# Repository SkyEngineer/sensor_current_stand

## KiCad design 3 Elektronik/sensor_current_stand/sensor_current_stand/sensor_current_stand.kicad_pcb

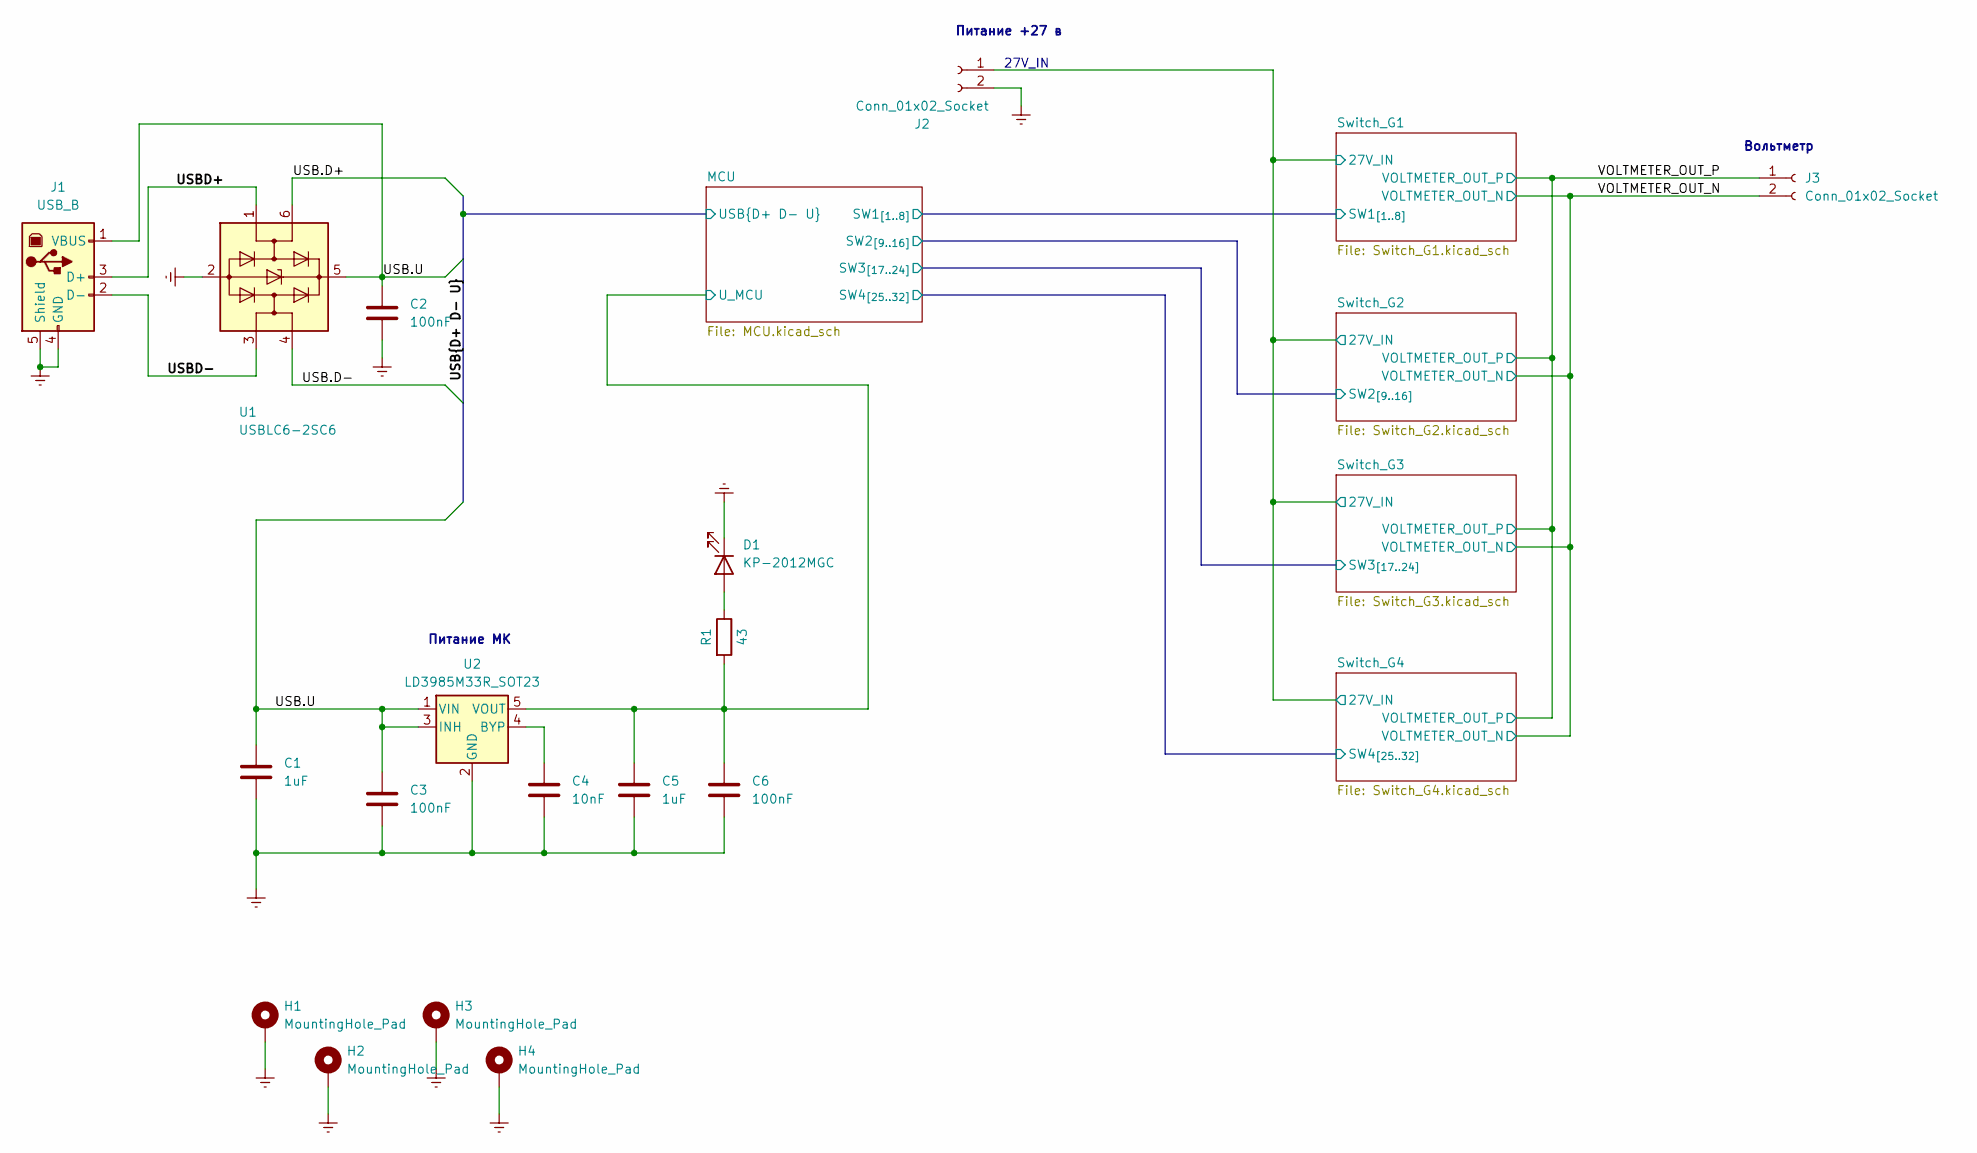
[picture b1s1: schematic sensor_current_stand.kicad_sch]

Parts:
C1, C5: 1uF; C_0805_2012Metric
C2, C3, C6: 100nF; C_0805_2012Metric
C4: 10nF; C_0805_2012Metric
D1: KP-2012MGC; LED_0805_2012Metric_Pad1.15x1.40mm_HandSolder
H1, H2, H3, H4: MountingHole_Pad; MountingHole_4.3mm_M4_Pad_TopBottom
J1: USB_B; USB_B_Lumberg_2411_02_Horizontal
J2, J3: Conn_01x02_Socket; JWT_A3963_1x02_P3.96mm_Vertical
R1: 43; R_1206_3216Metric_Pad1.30x1.75mm_HandSolder
U1: USBLC6-2SC6; SOT-23-6
U2: LD3985M33R_SOT23; SOT-23-5

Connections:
/MCU/U_MCU: C5.1, C6.1, R1.2, U2.5 (VOUT); also elsewhere on the board
/Switch_G1/27V_IN: J2.1; also elsewhere on the board
/USB.D+: U1.6 (I/O1); also elsewhere on the board
/USB.D-: U1.4 (I/O2); also elsewhere on the board
/USB.U: C1.1, C2.1, C3.1, J1.1 (VBUS), U1.5 (VBUS), U2.1 (VIN), U2.3 (INH)
/USBD+: J1.3 (D+), U1.1 (I/O1)
/USBD-: J1.2 (D-), U1.3 (I/O2)
/VOLTMETER_OUT_N: J3.2; also elsewhere on the board
/VOLTMETER_OUT_P: J3.1; also elsewhere on the board
unnamed: D1.2 (A), R1.1
unnamed: C4.1, U2.4 (BYP)

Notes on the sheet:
27V_IN
Вольтметр
Питание +27 в
Питание МК

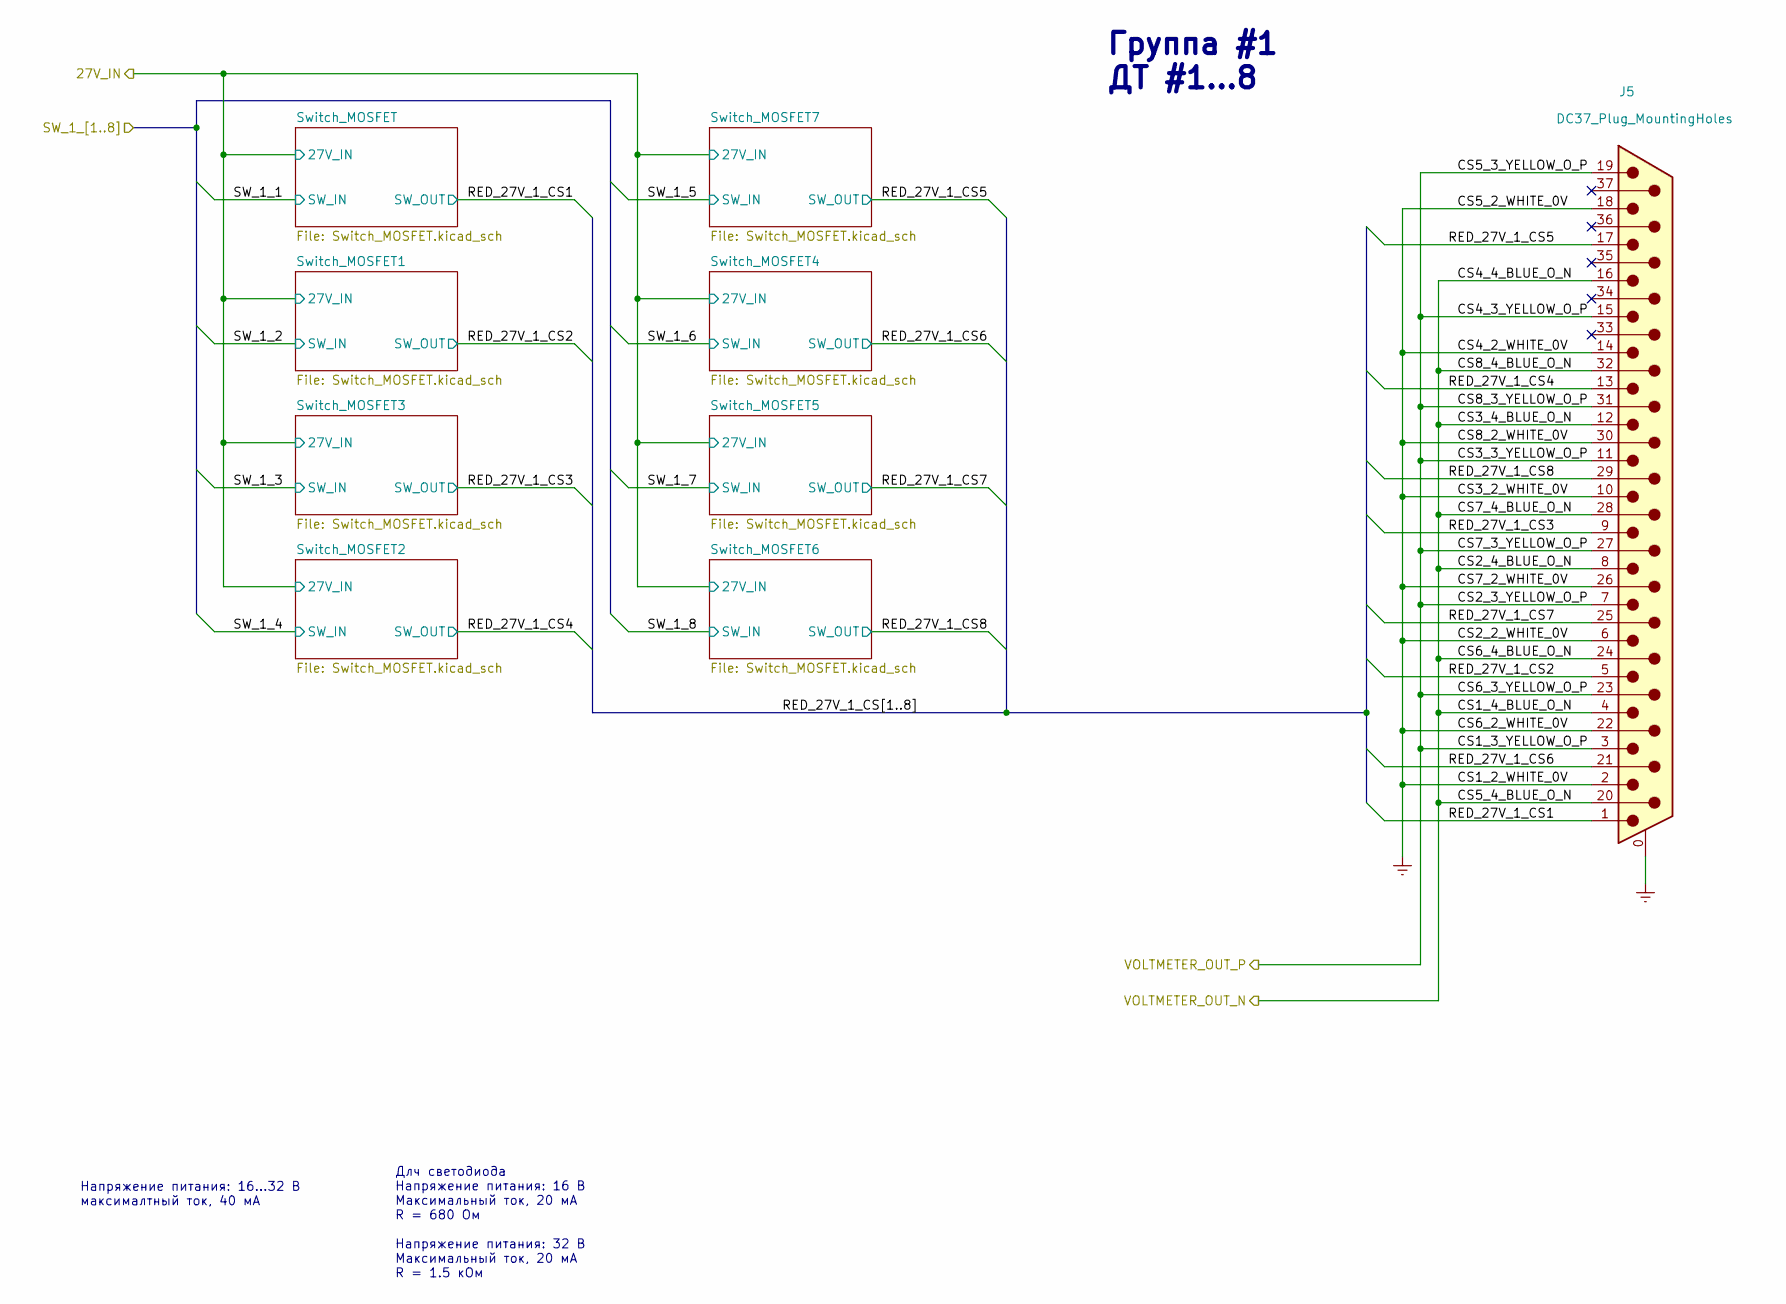
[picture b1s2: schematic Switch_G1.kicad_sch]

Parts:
J5: DC37_Plug_MountingHoles; DSUB-37_Male_Vertical_P2.77x2.84mm_MountingHoles

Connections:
/Switch_G1/27V_IN: J5.1, J5.5, J5.9, J5.13, J5.17, J5.21, J5.25, J5.29; also elsewhere on the board
/VOLTMETER_OUT_N: J5.4, J5.8, J5.12, J5.16, J5.20, J5.24, J5.28, J5.32; also elsewhere on the board
/VOLTMETER_OUT_P: J5.3, J5.7, J5.11, J5.15, J5.19, J5.23, J5.27, J5.31; also elsewhere on the board

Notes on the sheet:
Группа #1 ДТ #1...8
Длч светодиода Напряжение питания: 16 В Максимальный ток, 20 мА R = 680 Ом Напряжение питания: 32 В Максимальный ток, 20 мА R = 1.5 кОм
Напряжение питания: 16...32 В максималтный ток, 40 мА

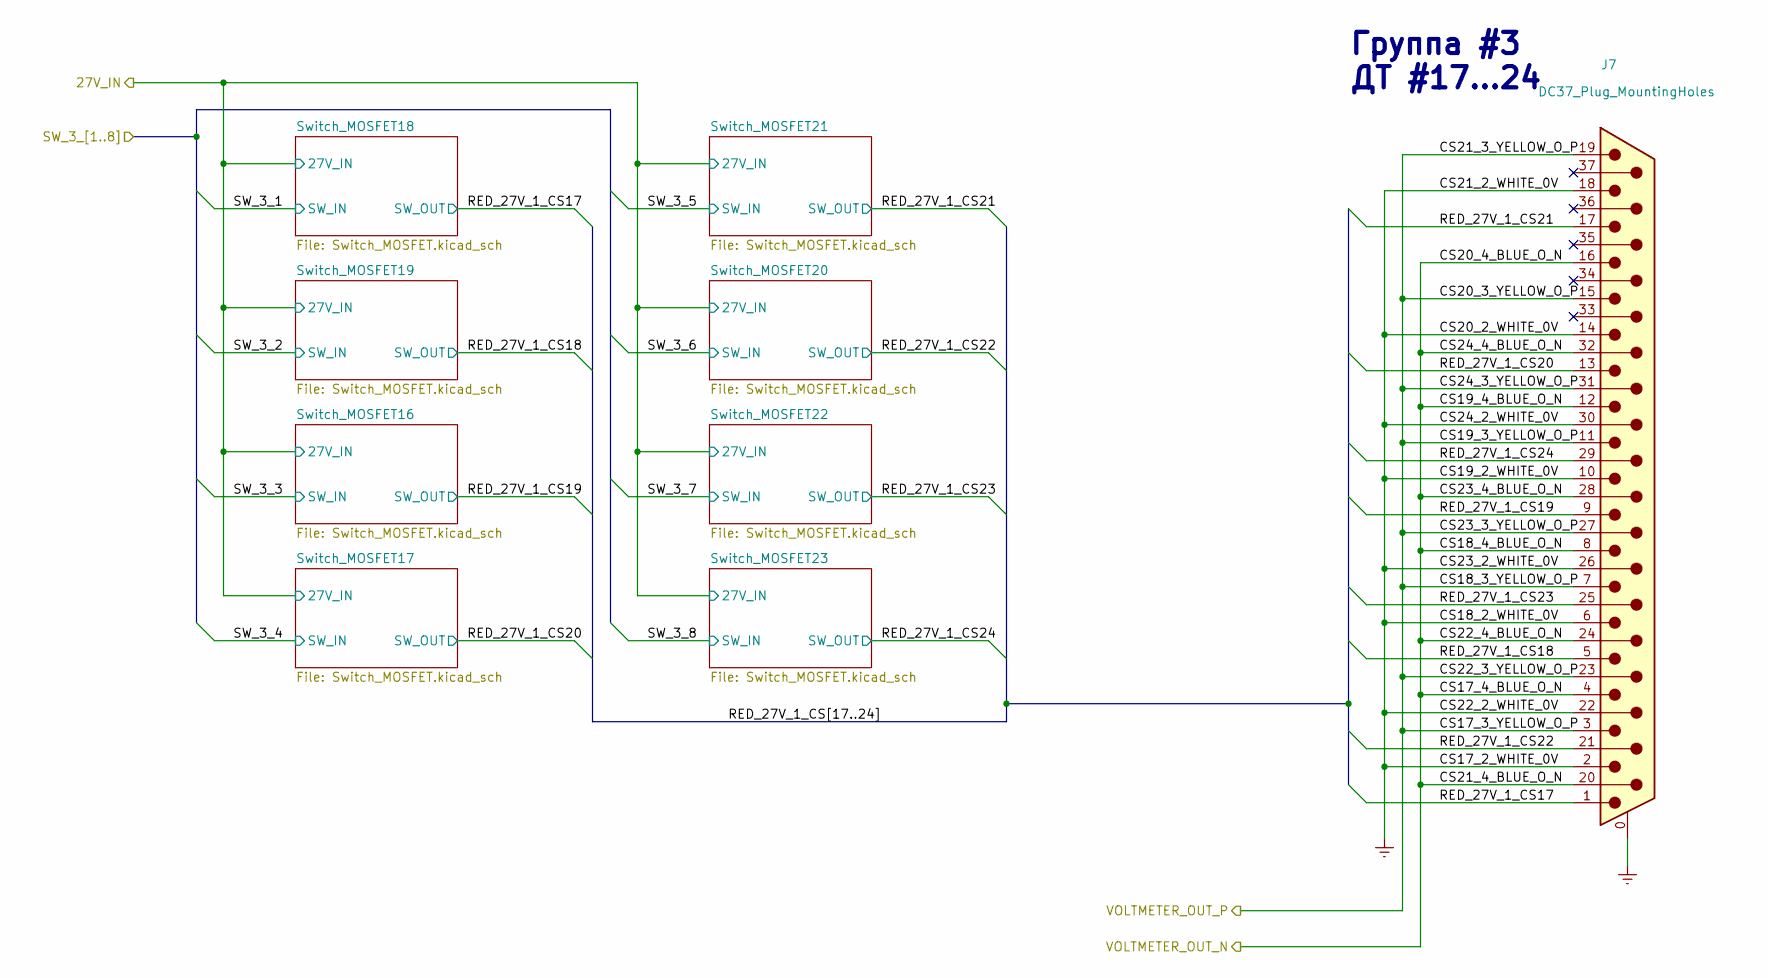
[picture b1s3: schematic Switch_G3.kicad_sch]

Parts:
J7: DC37_Plug_MountingHoles; DSUB-37_Male_Vertical_P2.77x2.84mm_MountingHoles

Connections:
/Switch_G1/27V_IN: J7.1, J7.5, J7.9, J7.13, J7.17, J7.21, J7.25, J7.29; also elsewhere on the board
/VOLTMETER_OUT_N: J7.4, J7.8, J7.12, J7.16, J7.20, J7.24, J7.28, J7.32; also elsewhere on the board
/VOLTMETER_OUT_P: J7.3, J7.7, J7.11, J7.15, J7.19, J7.23, J7.27, J7.31; also elsewhere on the board

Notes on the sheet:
Группа #3 ДТ #17...24

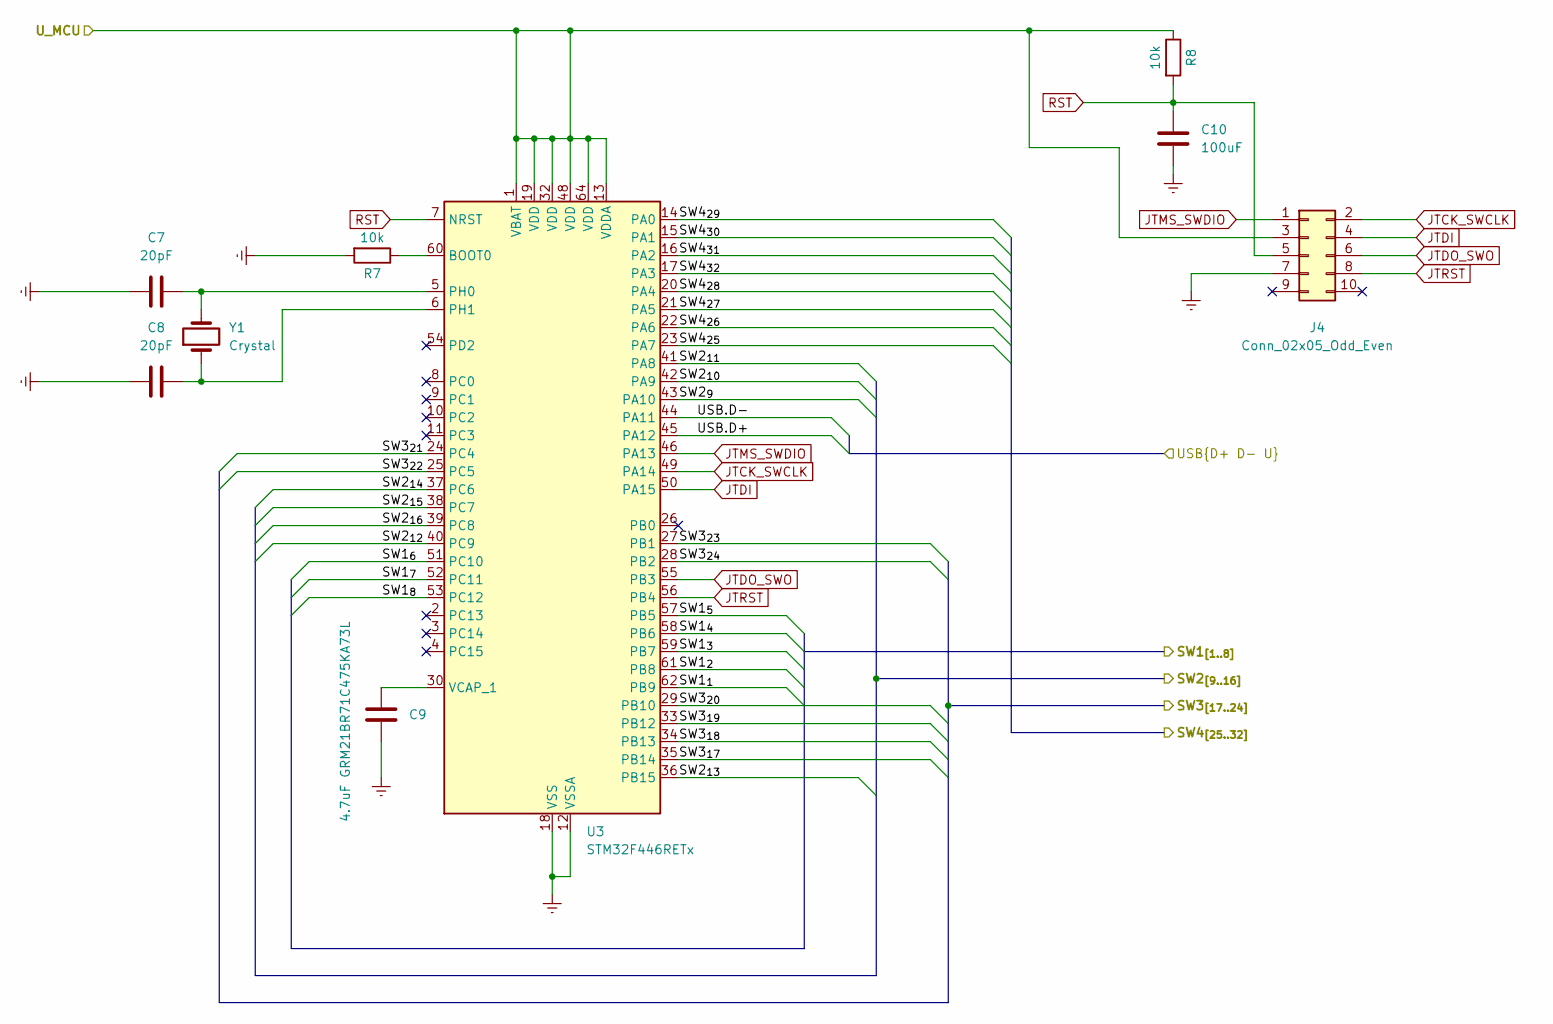
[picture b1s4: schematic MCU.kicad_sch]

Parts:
C7, C8: 20pF; C_0805_2012Metric_Pad1.18x1.45mm_HandSolder
C9: 4.7uF GRM21BR71C475KA73L; C_0805_2012Metric_Pad1.18x1.45mm_HandSolder
C10: 100uF; C_0805_2012Metric_Pad1.18x1.45mm_HandSolder
J4: Conn_02x05_Odd_Even; IDC-Header_2x05_P2.54mm_Vertical
R7, R8: 10k; R_1206_3216Metric_Pad1.30x1.75mm_HandSolder
U3: STM32F446RETx; LQFP-64_10x10mm_P0.5mm
Y1: Crystal; Crystal_HC49-U_Vertical

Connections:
/MCU/SW1_{1}: U3.62 (PB9); also elsewhere on the board
/MCU/SW1_{2}: U3.61 (PB8); also elsewhere on the board
/MCU/SW1_{3}: U3.59 (PB7); also elsewhere on the board
/MCU/SW1_{4}: U3.58 (PB6); also elsewhere on the board
/MCU/SW1_{5}: U3.57 (PB5); also elsewhere on the board
/MCU/SW1_{6}: U3.51 (PC10); also elsewhere on the board
/MCU/SW1_{7}: U3.52 (PC11); also elsewhere on the board
/MCU/SW1_{8}: U3.53 (PC12); also elsewhere on the board
/MCU/SW2_{9}: U3.43 (PA10); also elsewhere on the board
/MCU/SW2_{10}: U3.42 (PA9); also elsewhere on the board
/MCU/SW2_{11}: U3.41 (PA8); also elsewhere on the board
/MCU/SW2_{12}: U3.40 (PC9); also elsewhere on the board
/MCU/SW2_{13}: U3.36 (PB15); also elsewhere on the board
/MCU/SW2_{14}: U3.37 (PC6); also elsewhere on the board
/MCU/SW2_{15}: U3.38 (PC7); also elsewhere on the board
/MCU/SW2_{16}: U3.39 (PC8); also elsewhere on the board
/MCU/SW3_{17}: U3.35 (PB14); also elsewhere on the board
/MCU/SW3_{18}: U3.34 (PB13); also elsewhere on the board
/MCU/SW3_{19}: U3.33 (PB12); also elsewhere on the board
/MCU/SW3_{20}: U3.29 (PB10); also elsewhere on the board
/MCU/SW3_{21}: U3.24 (PC4); also elsewhere on the board
/MCU/SW3_{22}: U3.25 (PC5); also elsewhere on the board
/MCU/SW3_{23}: U3.27 (PB1); also elsewhere on the board
/MCU/SW3_{24}: U3.28 (PB2); also elsewhere on the board
/MCU/SW4_{25}: U3.23 (PA7); also elsewhere on the board
/MCU/SW4_{26}: U3.22 (PA6); also elsewhere on the board
/MCU/SW4_{27}: U3.21 (PA5); also elsewhere on the board
/MCU/SW4_{28}: U3.20 (PA4); also elsewhere on the board
/MCU/SW4_{29}: U3.14 (PA0); also elsewhere on the board
/MCU/SW4_{30}: U3.15 (PA1); also elsewhere on the board
/MCU/SW4_{31}: U3.16 (PA2); also elsewhere on the board
/MCU/SW4_{32}: U3.17 (PA3); also elsewhere on the board
/MCU/U_MCU: J4.3, R8.1, U3.1 (VBAT), U3.13 (VDDA), U3.19 (VDD), U3.32 (VDD), U3.48 (VDD), U3.64 (VDD); also elsewhere on the board
/USB.D+: U3.45 (PA12); also elsewhere on the board
/USB.D-: U3.44 (PA11); also elsewhere on the board
JTCK_SWCLK: J4.2, U3.49 (PA14)
JTDI: J4.4, U3.50 (PA15)
JTDO_SWO: J4.6, U3.55 (PB3)
JTMS_SWDIO: J4.1, U3.46 (PA13)
JTRST: J4.8, U3.56 (PB4)
unnamed: R7.1, U3.60 (BOOT0)
unnamed: C7.2, U3.5 (PH0), Y1.2
unnamed: C8.2, U3.6 (PH1), Y1.1
unnamed: C9.2, U3.30 (VCAP_1)
RST: C10.2, J4.5, R8.2, U3.7 (NRST)

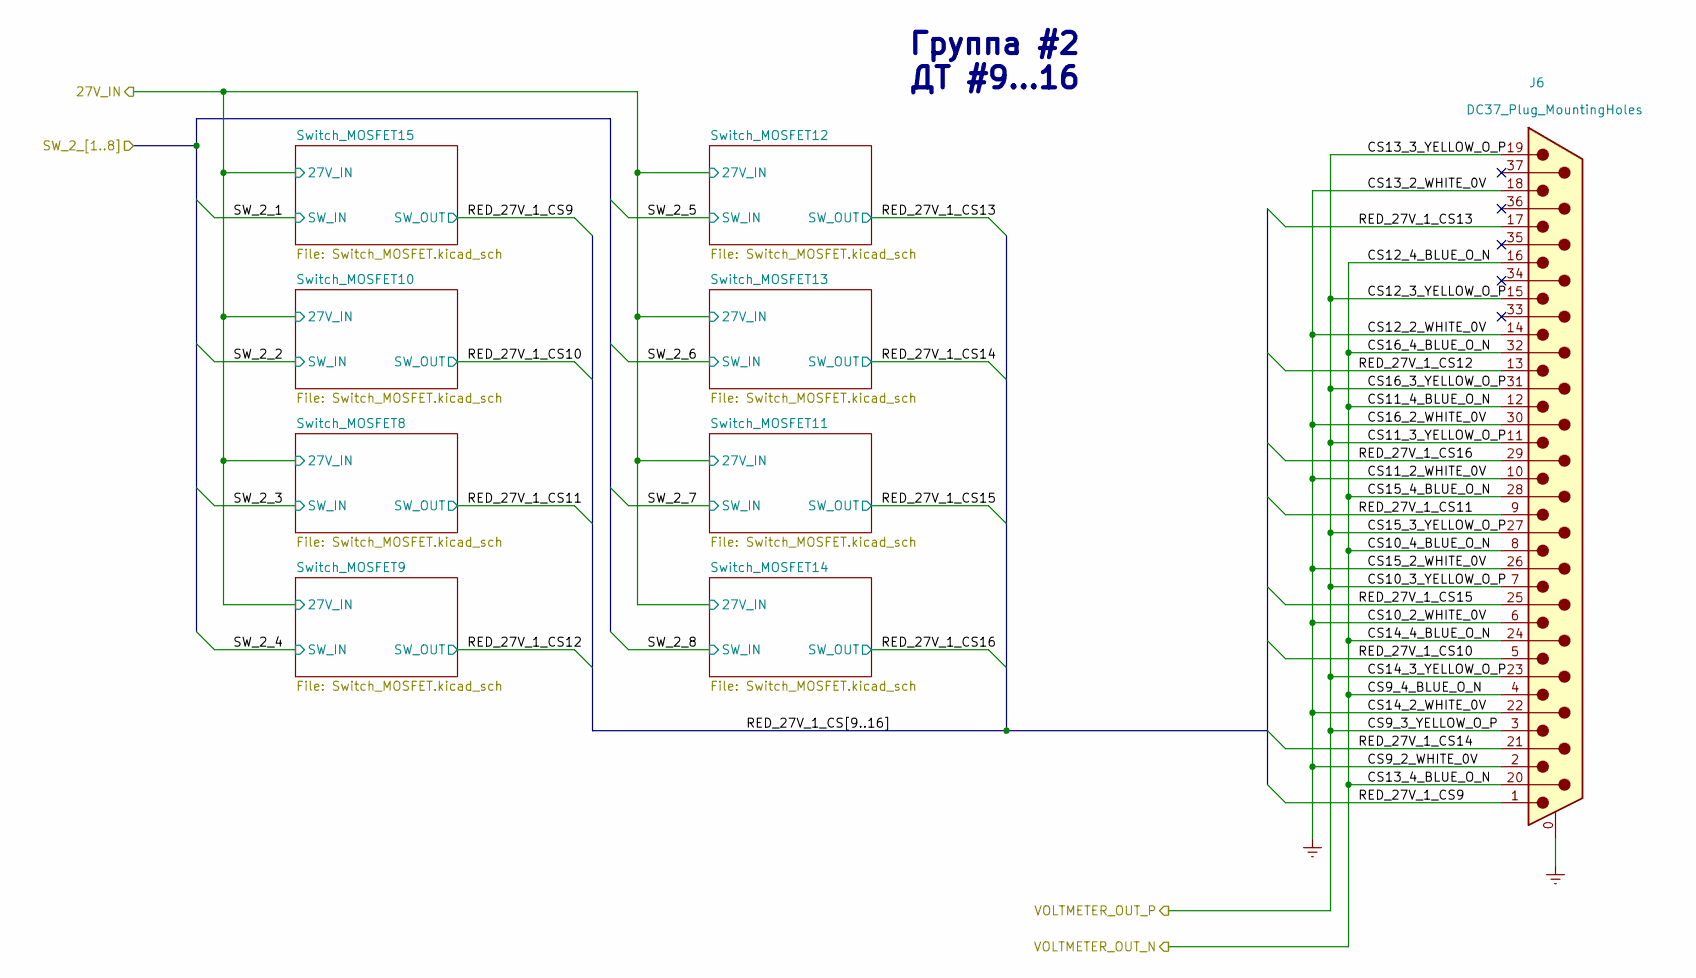
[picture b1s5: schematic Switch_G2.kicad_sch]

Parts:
J6: DC37_Plug_MountingHoles; DSUB-37_Male_Vertical_P2.77x2.84mm_MountingHoles

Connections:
/Switch_G1/27V_IN: J6.1, J6.5, J6.9, J6.13, J6.17, J6.21, J6.25, J6.29; also elsewhere on the board
/VOLTMETER_OUT_N: J6.4, J6.8, J6.12, J6.16, J6.20, J6.24, J6.28, J6.32; also elsewhere on the board
/VOLTMETER_OUT_P: J6.3, J6.7, J6.11, J6.15, J6.19, J6.23, J6.27, J6.31; also elsewhere on the board

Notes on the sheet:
Группа #2 ДТ #9...16

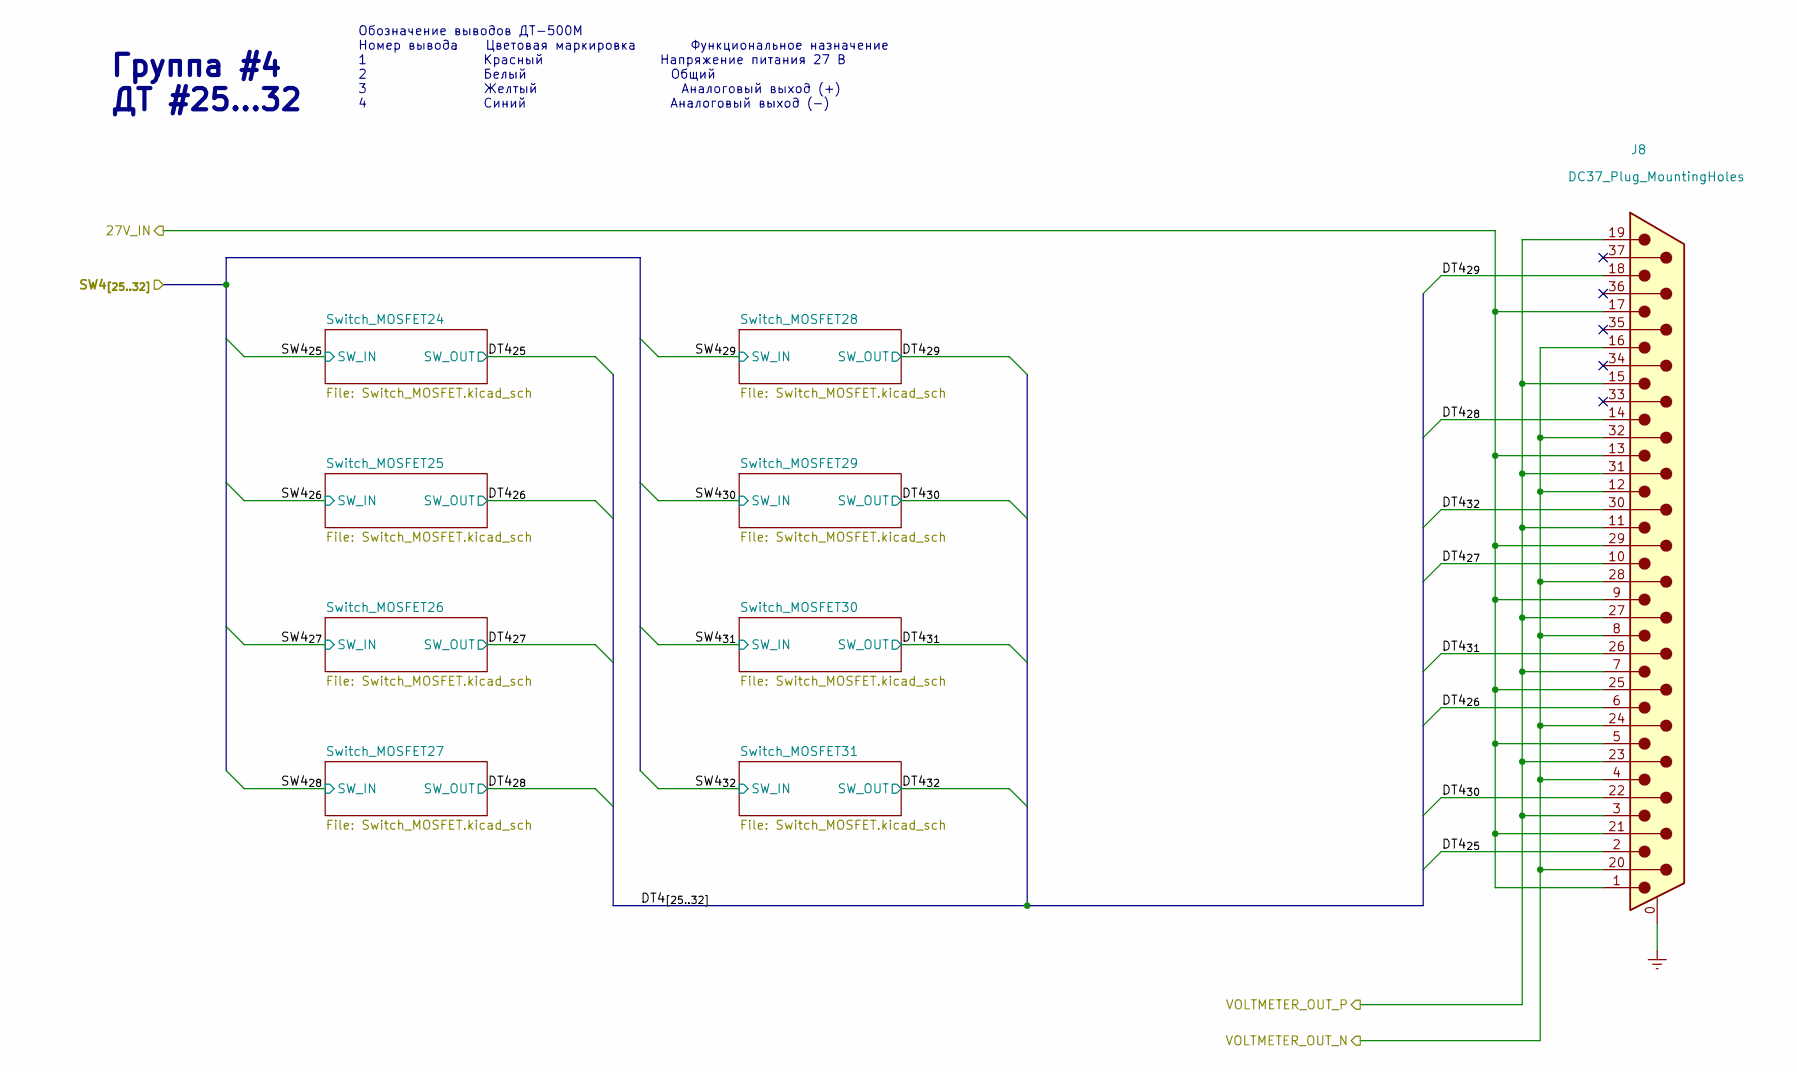
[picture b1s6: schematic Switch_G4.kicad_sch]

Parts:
J8: DC37_Plug_MountingHoles; DSUB-37_Male_Vertical_P2.77x2.84mm_MountingHoles

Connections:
/Switch_G1/27V_IN: J8.1, J8.5, J8.9, J8.13, J8.17, J8.21, J8.25, J8.29; also elsewhere on the board
/Switch_G4/DT4_{25}: J8.2; also elsewhere on the board
/Switch_G4/DT4_{26}: J8.6; also elsewhere on the board
/Switch_G4/DT4_{27}: J8.10; also elsewhere on the board
/Switch_G4/DT4_{28}: J8.14; also elsewhere on the board
/Switch_G4/DT4_{29}: J8.18; also elsewhere on the board
/Switch_G4/DT4_{30}: J8.22; also elsewhere on the board
/Switch_G4/DT4_{31}: J8.26; also elsewhere on the board
/Switch_G4/DT4_{32}: J8.30; also elsewhere on the board
/VOLTMETER_OUT_N: J8.4, J8.8, J8.12, J8.16, J8.20, J8.24, J8.28, J8.32; also elsewhere on the board
/VOLTMETER_OUT_P: J8.3, J8.7, J8.11, J8.15, J8.19, J8.23, J8.27, J8.31; also elsewhere on the board

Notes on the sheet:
Группа #4 ДТ #25...32
Обозначение выводов ДТ-500М Номер вывода Цветовая маркировка Функциональное назначение 1 Красный Напряжение питания 27 В 2 Белый Общий 3 Желтый Аналоговый выход (+) 4 Синий Аналоговый выход (-)

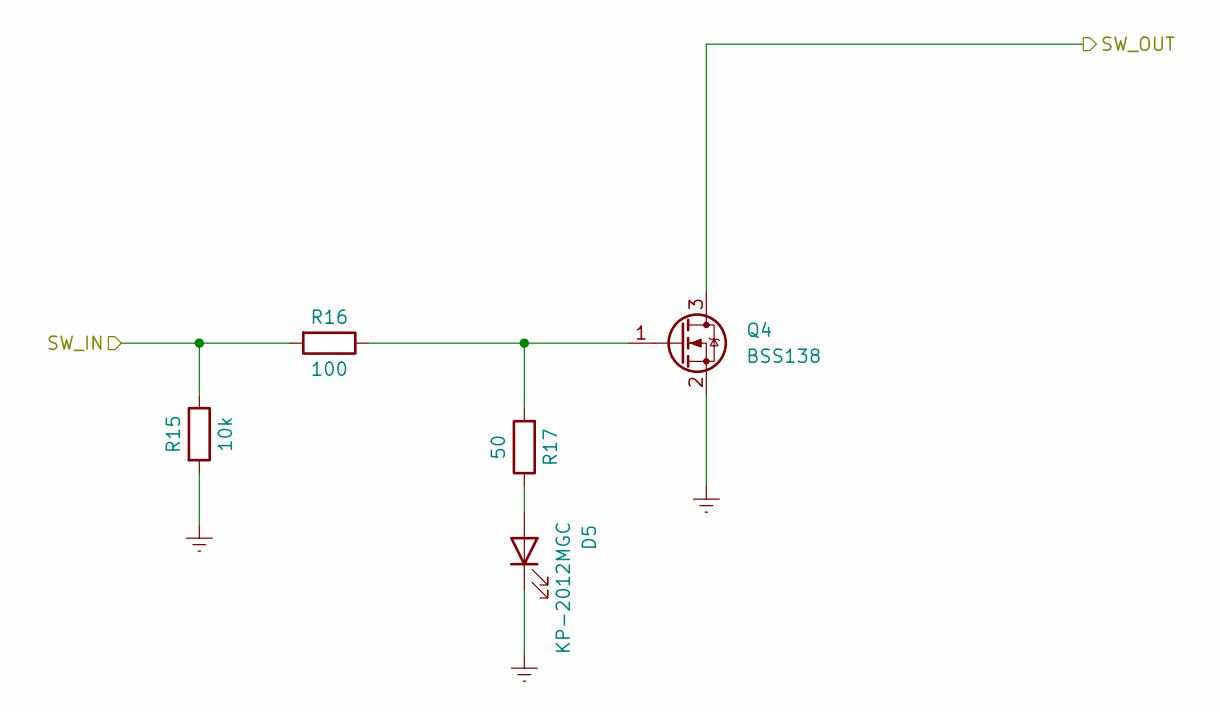
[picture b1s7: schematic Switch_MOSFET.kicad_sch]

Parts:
D5: KP-2012MGC; LED_0805_2012Metric_Pad1.15x1.40mm_HandSolder
Q4: BSS138; SOT-23
R15: 10k; R_1206_3216Metric_Pad1.30x1.75mm_HandSolder
R16: 100; R_1206_3216Metric_Pad1.30x1.75mm_HandSolder
R17: 50; R_1206_3216Metric_Pad1.30x1.75mm_HandSolder

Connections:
/MCU/SW1_{1}: R15.1, R16.2; also elsewhere on the board
unnamed: D5.2 (A), R17.1
unnamed: Q4.1 (G), R16.1, R17.2

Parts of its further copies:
D2, D3, D4, D6, D7, D8, D9, D10, D11, D12, D13, D14, D15, D16, D17, D18, D19, D20, D21, D22, D23, D24, D25, D26, D27, D28, D29, D30, D31, D32, D33: KP-2012MGC; LED_0805_2012Metric_Pad1.15x1.40mm_HandSolder
Q1, Q2, Q3, Q5, Q6, Q7, Q8, Q9, Q10, Q11, Q12, Q13, Q14, Q15, Q16, Q17, Q18, Q19, Q20, Q21, Q22, Q23, Q24, Q25, Q26, Q27, Q28, Q29, Q30, Q31, Q32: BSS138; SOT-23
R2, R9, R12, R18, R21, R24, R27, R30, R33, R36, R39, R42, R45, R48, R51, R54, R57, R60, R63, R66, R69, R72, R75, R78, R81, R84, R87, R90, R93, R96, R99: 10k; R_1206_3216Metric_Pad1.30x1.75mm_HandSolder
R3, R10, R13, R19, R22, R25, R28, R31, R34, R37, R40, R43, R46, R49, R52, R55, R58, R61, R64, R67, R70, R73, R76, R79, R82, R85, R88, R91, R94, R97, R100: 100; R_1206_3216Metric_Pad1.30x1.75mm_HandSolder
R4, R11, R14, R20, R23, R26, R29, R32, R35, R38, R41, R44, R47, R50, R53, R56, R59, R62, R65, R68, R71, R74, R77, R80, R83, R86, R89, R92, R95, R98, R101: 50; R_1206_3216Metric_Pad1.30x1.75mm_HandSolder

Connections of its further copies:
/MCU/SW1_{2}: R18.1, R19.2; also elsewhere on the board
/MCU/SW1_{3}: R21.1, R22.2; also elsewhere on the board
/MCU/SW1_{4}: R12.1, R13.2; also elsewhere on the board
/MCU/SW1_{5}: R24.1, R25.2; also elsewhere on the board
/MCU/SW1_{6}: R30.1, R31.2; also elsewhere on the board
/MCU/SW1_{7}: R33.1, R34.2; also elsewhere on the board
/MCU/SW1_{8}: R27.1, R28.2; also elsewhere on the board
/MCU/SW2_{9}: R36.1, R37.2; also elsewhere on the board
/MCU/SW2_{10}: R39.1, R40.2; also elsewhere on the board
/MCU/SW2_{11}: R54.1, R55.2; also elsewhere on the board
/MCU/SW2_{12}: R42.1, R43.2; also elsewhere on the board
/MCU/SW2_{13}: R51.1, R52.2; also elsewhere on the board
/MCU/SW2_{14}: R48.1, R49.2; also elsewhere on the board
/MCU/SW2_{15}: R45.1, R46.2; also elsewhere on the board
/MCU/SW2_{16}: R9.1, R10.2; also elsewhere on the board
/MCU/SW3_{17}: R57.1, R58.2; also elsewhere on the board
/MCU/SW3_{18}: R60.1, R61.2; also elsewhere on the board
/MCU/SW3_{19}: R69.1, R70.2; also elsewhere on the board
/MCU/SW3_{20}: R75.1, R76.2; also elsewhere on the board
/MCU/SW3_{21}: R78.1, R79.2; also elsewhere on the board
/MCU/SW3_{22}: R63.1, R64.2; also elsewhere on the board
/MCU/SW3_{23}: R66.1, R67.2; also elsewhere on the board
/MCU/SW3_{24}: R72.1, R73.2; also elsewhere on the board
/MCU/SW4_{25}: R2.1, R3.2; also elsewhere on the board
/MCU/SW4_{26}: R90.1, R91.2; also elsewhere on the board
/MCU/SW4_{27}: R87.1, R88.2; also elsewhere on the board
/MCU/SW4_{28}: R99.1, R100.2; also elsewhere on the board
/MCU/SW4_{29}: R96.1, R97.2; also elsewhere on the board
/MCU/SW4_{30}: R84.1, R85.2; also elsewhere on the board
/MCU/SW4_{31}: R81.1, R82.2; also elsewhere on the board
/MCU/SW4_{32}: R93.1, R94.2; also elsewhere on the board
/Switch_G4/DT4_{25}: Q1.3 (D); also elsewhere on the board
/Switch_G4/DT4_{26}: Q29.3 (D); also elsewhere on the board
/Switch_G4/DT4_{27}: Q28.3 (D); also elsewhere on the board
/Switch_G4/DT4_{28}: Q32.3 (D); also elsewhere on the board
/Switch_G4/DT4_{29}: Q31.3 (D); also elsewhere on the board
/Switch_G4/DT4_{30}: Q27.3 (D); also elsewhere on the board
/Switch_G4/DT4_{31}: Q26.3 (D); also elsewhere on the board
/Switch_G4/DT4_{32}: Q30.3 (D); also elsewhere on the board
unnamed: D2.2 (A), R4.1
unnamed: D3.2 (A), R11.1
unnamed: D4.2 (A), R14.1
unnamed: D6.2 (A), R20.1
unnamed: D7.2 (A), R23.1
unnamed: D8.2 (A), R26.1
unnamed: D9.2 (A), R29.1
unnamed: D10.2 (A), R32.1
unnamed: D11.2 (A), R35.1
unnamed: D12.2 (A), R38.1
unnamed: D13.2 (A), R41.1
unnamed: D14.2 (A), R44.1
unnamed: D15.2 (A), R47.1
unnamed: D16.2 (A), R50.1
unnamed: D17.2 (A), R53.1
unnamed: D18.2 (A), R56.1
unnamed: D19.2 (A), R59.1
unnamed: D20.2 (A), R62.1
unnamed: D21.2 (A), R65.1
unnamed: D22.2 (A), R68.1
unnamed: D23.2 (A), R71.1
unnamed: D24.2 (A), R74.1
unnamed: D25.2 (A), R77.1
unnamed: D26.2 (A), R80.1
unnamed: D27.2 (A), R83.1
unnamed: D28.2 (A), R86.1
unnamed: D29.2 (A), R89.1
unnamed: D30.2 (A), R92.1
unnamed: D31.2 (A), R95.1
unnamed: D32.2 (A), R98.1
unnamed: D33.2 (A), R101.1
unnamed: Q1.1 (G), R3.1, R4.2
unnamed: Q2.1 (G), R10.1, R11.2
unnamed: Q3.1 (G), R13.1, R14.2
unnamed: Q5.1 (G), R19.1, R20.2
unnamed: Q6.1 (G), R22.1, R23.2
unnamed: Q7.1 (G), R25.1, R26.2
unnamed: Q8.1 (G), R28.1, R29.2
unnamed: Q9.1 (G), R31.1, R32.2
unnamed: Q10.1 (G), R34.1, R35.2
unnamed: Q11.1 (G), R37.1, R38.2
unnamed: Q12.1 (G), R40.1, R41.2
unnamed: Q13.1 (G), R43.1, R44.2
unnamed: Q14.1 (G), R46.1, R47.2
unnamed: Q15.1 (G), R49.1, R50.2
unnamed: Q16.1 (G), R52.1, R53.2
unnamed: Q17.1 (G), R55.1, R56.2
unnamed: Q18.1 (G), R58.1, R59.2
unnamed: Q19.1 (G), R61.1, R62.2
unnamed: Q20.1 (G), R64.1, R65.2
unnamed: Q21.1 (G), R67.1, R68.2
unnamed: Q22.1 (G), R70.1, R71.2
unnamed: Q23.1 (G), R73.1, R74.2
unnamed: Q24.1 (G), R76.1, R77.2
unnamed: Q25.1 (G), R79.1, R80.2
unnamed: Q26.1 (G), R82.1, R83.2
unnamed: Q27.1 (G), R85.1, R86.2
unnamed: Q28.1 (G), R88.1, R89.2
unnamed: Q29.1 (G), R91.1, R92.2
unnamed: Q30.1 (G), R94.1, R95.2
unnamed: Q31.1 (G), R97.1, R98.2
unnamed: Q32.1 (G), R100.1, R101.2

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
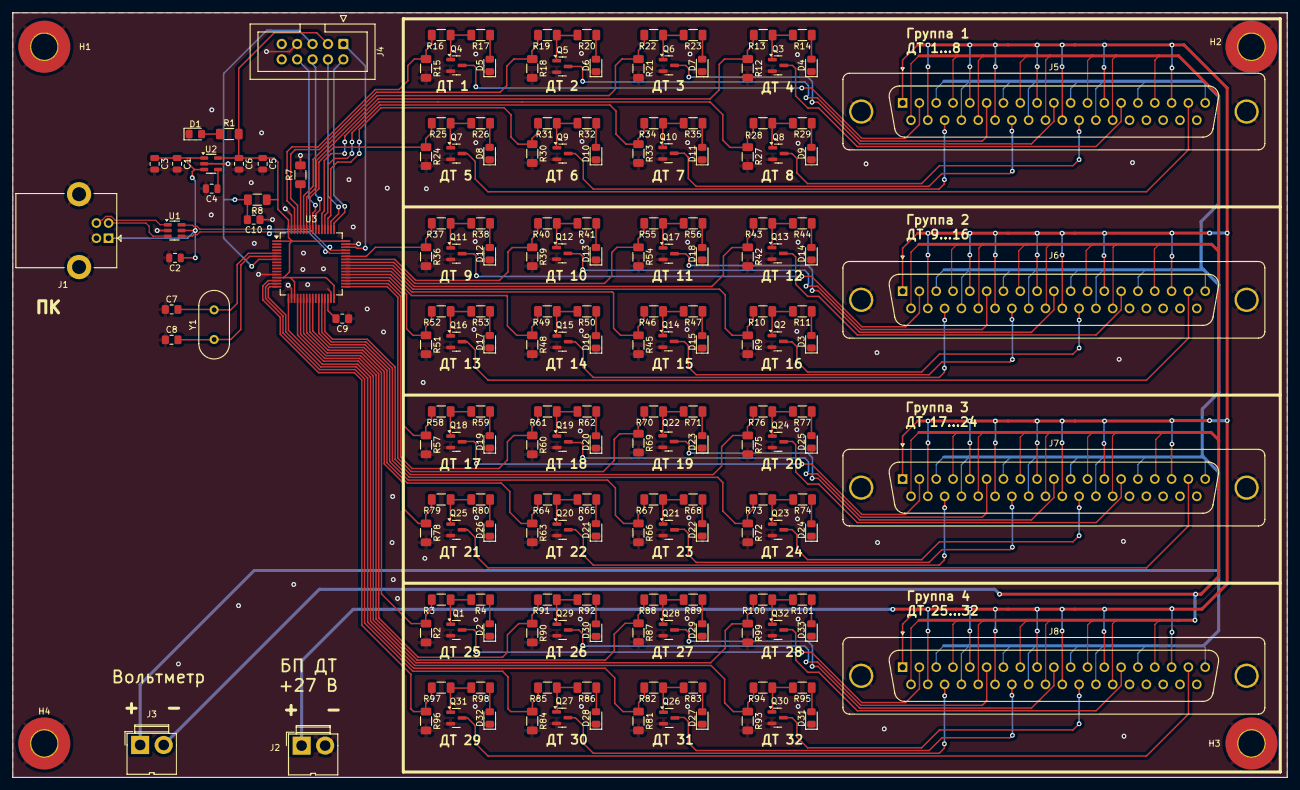
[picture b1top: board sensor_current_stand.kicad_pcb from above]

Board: 2 copper layers, 210.0 x 126.0 mm, 190 parts (0 on the bottom side), 150 nets.

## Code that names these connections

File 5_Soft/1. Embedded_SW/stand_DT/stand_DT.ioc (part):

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Mcu.Name=STM32F446R(C-E)Tx
Mcu.Package=LQFP64
Mcu.UserName=STM32F446RETx
PA0-WKUP.GPIOParameters=GPIO_Label
PA0-WKUP.GPIO_Label=SW4_29
PA0-WKUP.Signal=GPIO_Output
PA1.GPIOParameters=GPIO_Label
PA1.GPIO_Label=SW4_30
PA1.Signal=GPIO_Output
PA10.GPIOParameters=GPIO_Label
PA10.GPIO_Label=SW2_9
PA10.Signal=GPIO_Output
PA11.Mode=Device_Only
PA11.Signal=USB_OTG_FS_DM
PA12.Mode=Device_Only
PA12.Signal=USB_OTG_FS_DP
PA13.Mode=JTAG_5_pins
PA13.Signal=SYS_JTMS-SWDIO
PA14.Mode=JTAG_5_pins
PA14.Signal=SYS_JTCK-SWCLK
PA15.Mode=JTAG_5_pins
PA15.Signal=SYS_JTDI
PA2.GPIOParameters=GPIO_Label
PA2.GPIO_Label=SW4_31
PA2.Signal=GPIO_Output
PA3.GPIOParameters=GPIO_Label
PA3.GPIO_Label=SW4_32
PA3.Signal=GPIO_Output
PA4.GPIOParameters=GPIO_Label
PA4.GPIO_Label=SW4_28
PA4.Signal=GPIO_Output
PA5.GPIOParameters=GPIO_Label
PA5.GPIO_Label=SW4_27
PA5.Signal=GPIO_Output
PA6.GPIOParameters=GPIO_Label
PA6.GPIO_Label=SW4_26
PA6.Signal=GPIO_Output
PA7.GPIOParameters=GPIO_Label
PA7.GPIO_Label=SW4_25
PA7.Signal=GPIO_Output
PA8.GPIOParameters=GPIO_Label
PA8.GPIO_Label=SW2_11
PA8.Signal=GPIO_Output
PA9.GPIOParameters=GPIO_Label
PA9.GPIO_Label=SW2_10
PA9.Signal=GPIO_Output
PB1.GPIOParameters=GPIO_Label
PB1.GPIO_Label=SW3_23
PB1.Signal=GPIO_Output
PB10.GPIOParameters=GPIO_Label
PB10.GPIO_Label=SW3_20
PB10.Signal=GPIO_Output
PB12.GPIOParameters=GPIO_Label
PB12.GPIO_Label=SW3_19
PB12.Signal=GPIO_Output
PB13.GPIOParameters=GPIO_Label
PB13.GPIO_Label=SW3_18
PB13.Signal=GPIO_Output
PB14.GPIOParameters=GPIO_Label
PB14.GPIO_Label=SW3_17
PB14.Signal=GPIO_Output
PB15.GPIOParameters=GPIO_Label
PB15.GPIO_Label=SW2_13
PB15.Signal=GPIO_Output
PB2.GPIOParameters=GPIO_Label
PB2.GPIO_Label=SW3_24
PB2.Signal=GPIO_Output
PB3.Mode=JTAG_5_pins
PB3.Signal=SYS_JTDO-SWO
PB4.Mode=JTAG_5_pins
PB4.Signal=SYS_JTRST
PB5.GPIOParameters=GPIO_Label
PB5.GPIO_Label=SW1_5
PB5.Signal=GPIO_Output
PB6.GPIOParameters=GPIO_Label
PB6.GPIO_Label=SW1_4
PB6.Signal=GPIO_Output
PB7.GPIOParameters=GPIO_Label
PB7.GPIO_Label=SW1_3
PB7.Signal=GPIO_Output
PB8.GPIOParameters=GPIO_Label
PB8.GPIO_Label=SW1_2
PB8.Signal=GPIO_Output
PB9.GPIOParameters=GPIO_Label
PB9.GPIO_Label=SW1_1
PB9.Signal=GPIO_Output
PC10.GPIOParameters=GPIO_Label
PC10.GPIO_Label=SW1_6
PC10.Signal=GPIO_Output
PC11.GPIOParameters=GPIO_Label
PC11.GPIO_Label=SW1_7
PC11.Signal=GPIO_Output
PC12.GPIOParameters=GPIO_Label
PC12.GPIO_Label=SW1_8
PC12.Signal=GPIO_Output
PC4.GPIOParameters=GPIO_Label
PC4.GPIO_Label=SW3_21
PC4.Signal=GPIO_Output
PC5.GPIOParameters=GPIO_Label
PC5.GPIO_Label=SW3_22
PC5.Signal=GPIO_Output
PC6.GPIOParameters=GPIO_Label
PC6.GPIO_Label=SW2_14
PC6.Signal=GPIO_Output
PC7.GPIOParameters=GPIO_Label
PC7.GPIO_Label=SW2_15
PC7.Signal=GPIO_Output
PC8.GPIOParameters=GPIO_Label
PC8.GPIO_Label=SW2_16
PC8.Signal=GPIO_Output
PC9.GPIOParameters=GPIO_Label
PC9.GPIO_Label=SW2_12
PC9.Signal=GPIO_Output
PH0-OSC_IN.Mode=HSE-External-Oscillator
PH0-OSC_IN.Signal=RCC_OSC_IN
PH1-OSC_OUT.Mode=HSE-External-Oscillator
PH1-OSC_OUT.Signal=RCC_OSC_OUT
RCC.HSE_VALUE=14000000
RCC.SYSCLKFreq_VALUE=32000000
RCC.SYSCLKSource=RCC_SYSCLKSOURCE_PLLCLK
board=custom

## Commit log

2024-04-04 Размещение
2024-04-04 0 Vom Auftraggeber
2024-04-04 норм архитектура
2024-04-05 start
2024-04-10 разработка
2024-04-10 архивы
2024-04-10 STM soft
    создание софта для общения с ПК на STM. Сейчас проект написан под STM32F3Discovery для отладки технических решений
2024-04-10 quarz
2024-04-11 MUX sheet готово
2024-04-11 secondary supply готово
2024-04-11 промежуточная версия
    надо правильно подключить прошивалку
2024-04-17 Группа 1 разведена но не проверена
2024-04-19 трассировка
2024-04-19 переписка
2024-04-22 прверка на производстве
2024-04-23 счета
2024-04-24 окружение для тестового проекта STM_F4_DISC
2024-04-24 Kicad 8
2024-04-24 черновики договоров
2024-04-24 Desktop
2024-04-25 STM готов к отладке
2024-04-25 STM готово к отладке
2024-04-25 придирка к пробелам
2024-05-03 test_stand
2024-05-09 Version 2
2024-05-10 v2 GEREBER
2024-05-10 V2 GERBER
2024-05-13 summary comit
2024-05-13 delete
2024-05-13 new version
2024-05-14 ui desktop
2024-05-27 подготовка к отладке
2024-06-01 отладка
2024-06-03 отладка 2
2024-06-04 отработка
    не удается установить только общение нормально с БП измеряемого тока
2024-06-17 ПО в МК
2024-06-30 проект завершён
2024-08-14 копиии
